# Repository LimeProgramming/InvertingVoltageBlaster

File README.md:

# InvertingVoltageBlaster
Changing necrowares voltageblaster to use a buckboost regulator instead of an lm7905

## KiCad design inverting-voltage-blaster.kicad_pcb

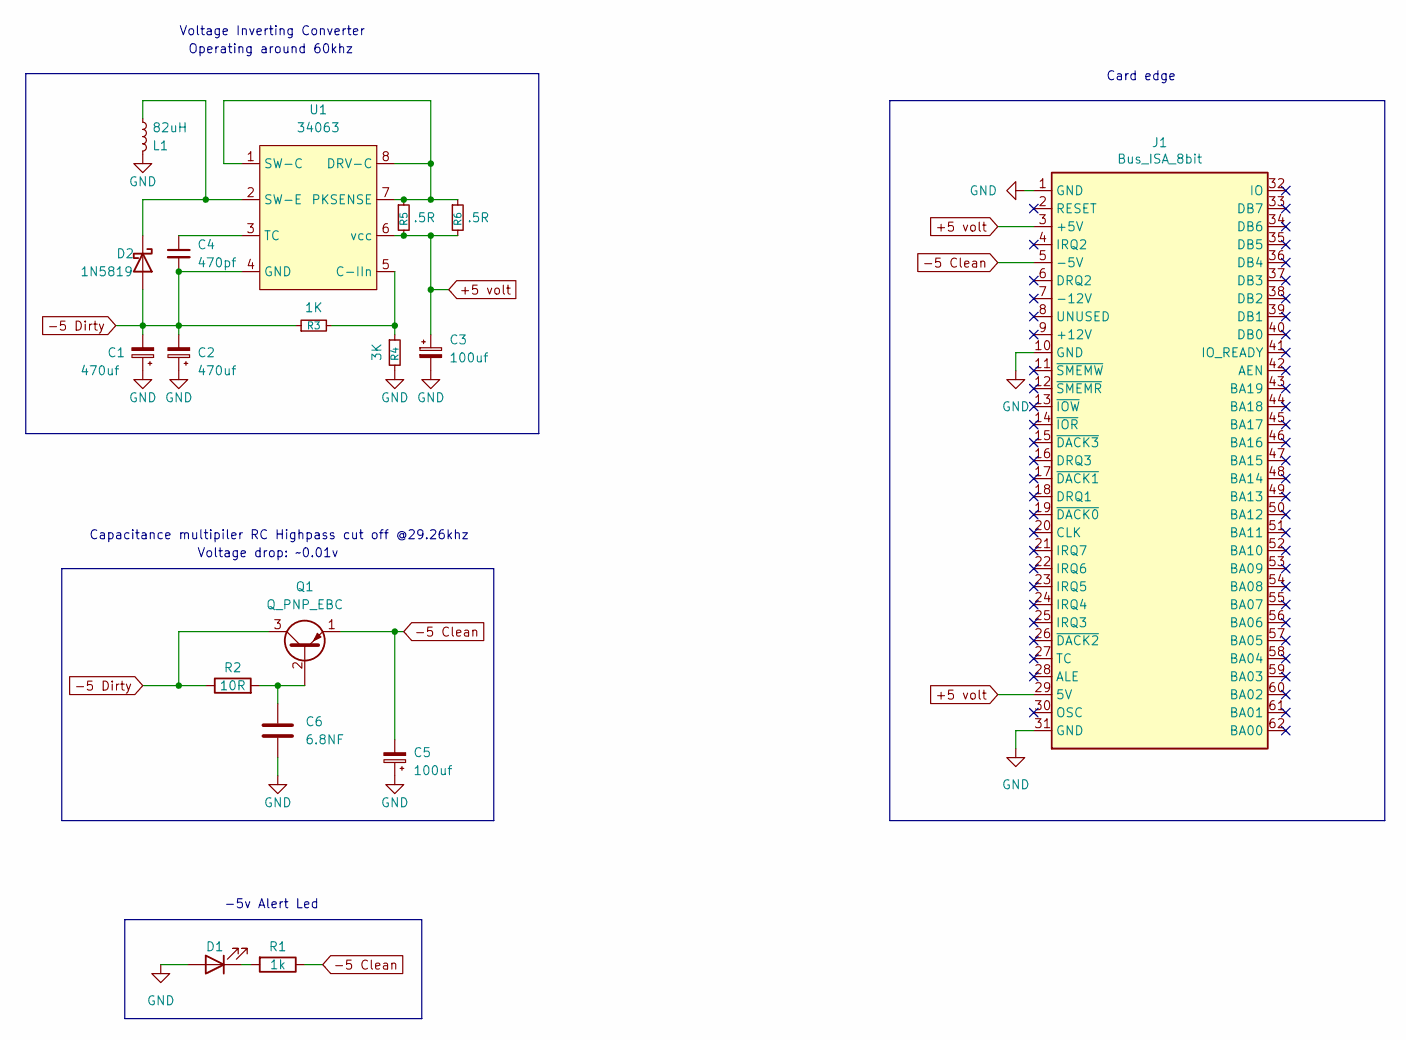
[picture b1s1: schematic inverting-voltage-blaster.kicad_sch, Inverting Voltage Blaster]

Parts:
C1, C2: 470uf; CP_Radial_D8.0mm_P3.50mm; LCSC1 C44604
C3: 100uf; CP_Radial_D6.3mm_P2.50mm; LCSC C338170
C4: 470pf; C_0805_2012Metric; LCSC C62771
C5: 100uf; CP_Radial_D6.3mm_P2.50mm
C6: 6.8NF; C_0805_2012Metric; LCSC C77068
D1: -5V; LED_D5.0mm; LCSC C99697
D2: 1N5819; D_SOD-123; LCSC C82544
J1: Bus_ISA_8bit; ISA_8BIT_EDGE
L1: 82uH; L_12x12mm_H4.5mm; LCSC C329753
Q1: Q_PNP_EBC; SOT-89-3_Handsoldering; LCSC C9656
R1: 1k; C_0805_2012Metric; LCSC C309081
R2: 10R; C_0805_2012Metric; LCSC C724882
R3: 1K; C_0805_2012Metric; LCSC C309081
R4: 3K; C_0805_2012Metric; LCSC C2984389
R5, R6: .5R; C_0805_2012Metric; LCSC C2998169
U1: 34063; CH340N; LCSC C521144

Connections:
+5 volt: C3.1, J1.3 (+5V), J1.29 (5V), R5.2, R6.2, U1.6 (vcc)
-5 Clean: C5.2, J1.5 (-5V), Q1.1 (E), R1.1
-5 Dirty: C1.2, C2.2, C4.2, D2.2 (A), Q1.3 (C), R2.1, R3.1, U1.4 (GND)
GND: C1.1, C2.1, C3.2, C5.1, C6.2, D1.2 (A), J1.1 (GND), J1.10 (GND), J1.31 (GND), L1.2, R4.2
unnamed: C4.1, U1.3 (TC)
unnamed: C6.1, Q1.2 (B), R2.2
unnamed: D1.1 (K), R1.2
unnamed: D2.1 (K), L1.1, U1.2 (SW-E)
unnamed: R3.2, R4.1, U1.5 (C-IIn)
unnamed: R5.1, R6.1, U1.1 (SW-C), U1.7 (PKSENSE), U1.8 (DRV-C)

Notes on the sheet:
-5v Alert Led
Voltage Inverting Converter
Voltage drop: ~0.01v
Operating around 60khz
Card edge
Capacitance multipiler RC Highpass cut off @29.26khz

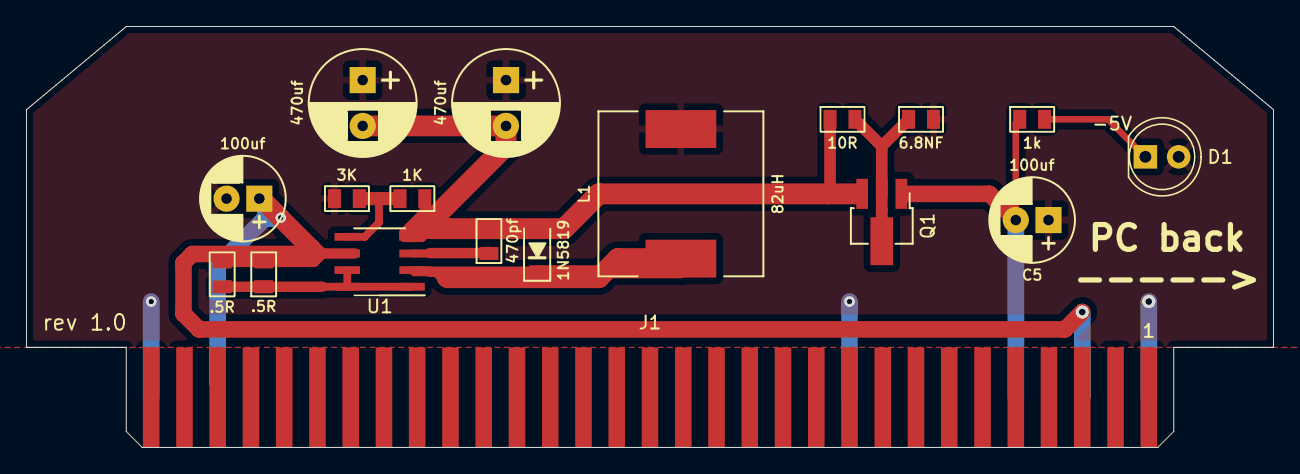
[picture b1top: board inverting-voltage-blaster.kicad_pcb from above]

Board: 2 copper layers, 95.2 x 32.2 mm, 18 parts (0 on the bottom side), 10 nets.

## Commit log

2022-10-31 init upload
